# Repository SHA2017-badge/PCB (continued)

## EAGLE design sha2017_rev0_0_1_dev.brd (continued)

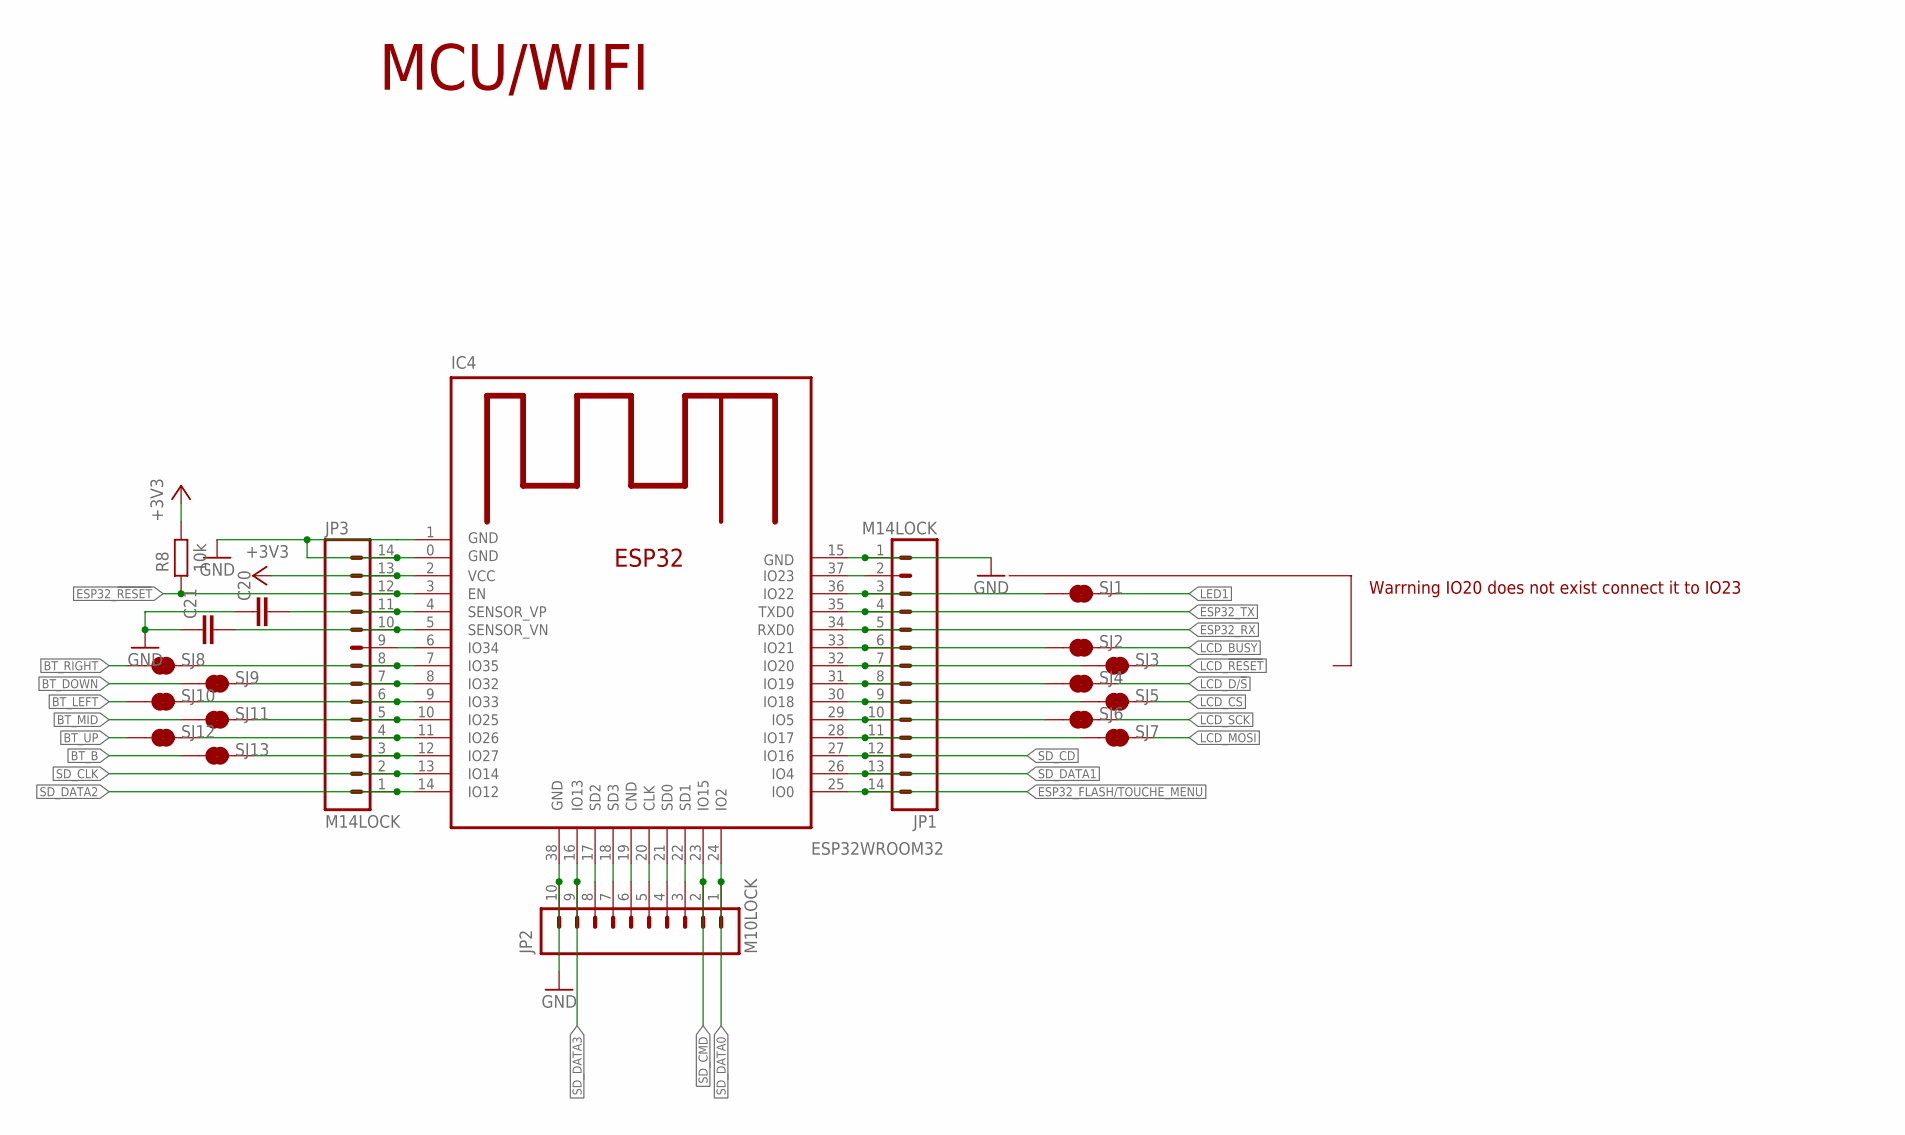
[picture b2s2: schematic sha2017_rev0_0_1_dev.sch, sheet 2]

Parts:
C20, C21: C-EUC0603; C0603
IC4: ESP32WROOM32; ESP32MOD
JP1, JP3: M14LOCK; 1X14_LOCK
JP2: M10LOCK; 1X10_LOCK
R8: 10k; R0603; PARTNO ERJ-3GEYJ103V
SJ1, SJ2, SJ3, SJ4, SJ5, SJ6, SJ7, SJ8, SJ9, SJ10, SJ11, SJ12, SJ13: JUMPER-PAD-2-NC_BY_TRACE; PAD-JUMPER-2-NC_BY_TRACE_YES_SILK

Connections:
+3V3: IC4.2 (VCC), JP3.13, R8.1; also elsewhere on the board
BT_B: SJ13.1; also elsewhere on the board
BT_DOWN: SJ9.1; also elsewhere on the board
BT_LEFT: SJ10.1; also elsewhere on the board
BT_MID: SJ11.1; also elsewhere on the board
BT_RIGHT: SJ8.1; also elsewhere on the board
BT_UP: SJ12.1; also elsewhere on the board
ESP32_!RESET: IC4.3 (EN), JP3.12, R8.2; also elsewhere on the board
ESP32_FLASH/TOUCHE_MENU: IC4.25 (IO0), JP1.14; also elsewhere on the board
ESP32_RX: IC4.34 (RXD0), JP1.5; also elsewhere on the board
ESP32_TX: IC4.35 (TXD0), JP1.4; also elsewhere on the board
GND: C20.1, C21.1, IC4.0 (GND), IC4.1 (GND), IC4.15 (GND), IC4.38 (GND), JP1.1, JP2.10, JP3.14; also elsewhere on the board
LCD_!RESET: SJ3.2; also elsewhere on the board
LCD_BUSY: SJ2.2; also elsewhere on the board
LCD_CS: SJ5.2; also elsewhere on the board
LCD_D/!S: SJ4.2; also elsewhere on the board
LCD_MOSI: SJ7.2; also elsewhere on the board
LCD_SCK: SJ6.2; also elsewhere on the board
LED1: SJ1.2; also elsewhere on the board
unnamed: IC4.6 (IO34), JP3.9
unnamed: IC4.17 (SD2), JP2.8
unnamed: IC4.18 (SD3), JP2.7
unnamed: IC4.19 (CND), JP2.6
unnamed: IC4.20 (CLK), JP2.5
unnamed: IC4.21 (SD0), JP2.4
unnamed: IC4.22 (SD1), JP2.3
unnamed: IC4.37 (IO23), JP1.2
unnamed: IC4.36 (IO22), JP1.3, SJ1.1
unnamed: IC4.33 (IO21), JP1.6, SJ2.1
unnamed: IC4.32 (IO20), JP1.7, SJ3.1
unnamed: IC4.30 (IO18), JP1.9, SJ5.1
unnamed: IC4.29 (IO5), JP1.10, SJ6.1
unnamed: IC4.28 (IO17), JP1.11, SJ7.1
unnamed: C20.2, IC4.4 (SENSOR_VP), JP3.11
unnamed: C21.2, IC4.5 (SENSOR_VN), JP3.10
unnamed: IC4.7 (IO35), JP3.8, SJ8.2
unnamed: IC4.8 (IO32), JP3.7, SJ9.2
unnamed: IC4.9 (IO33), JP3.6, SJ10.2
unnamed: IC4.10 (IO25), JP3.5, SJ11.2
unnamed: IC4.11 (IO26), JP3.4, SJ12.2
unnamed: IC4.12 (IO27), JP3.3, SJ13.2
unnamed: IC4.31 (IO19), JP1.8, SJ4.1
SD_CD: IC4.27 (IO16), JP1.12; also elsewhere on the board
SD_CLK: IC4.13 (IO14), JP3.2; also elsewhere on the board
SD_CMD: IC4.23 (IO15), JP2.2; also elsewhere on the board
SD_DATA0: IC4.24 (IO2), JP2.1; also elsewhere on the board
SD_DATA1: IC4.26 (IO4), JP1.13; also elsewhere on the board
SD_DATA2: IC4.14 (IO12), JP3.1; also elsewhere on the board
SD_DATA3: IC4.16 (IO13), JP2.9; also elsewhere on the board

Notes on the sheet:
MCU/WIFI
Warrning IO20 does not exist connect it to IO23

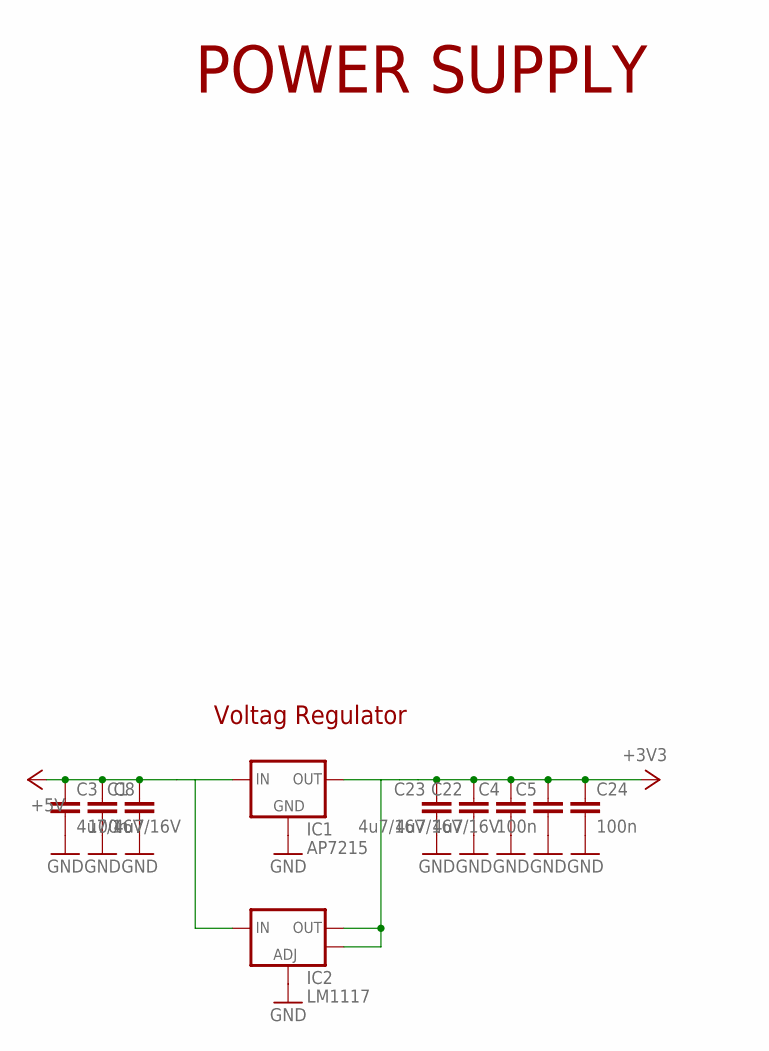
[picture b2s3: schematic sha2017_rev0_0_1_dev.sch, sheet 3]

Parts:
C1, C5, C24: 100n; C0603; PARTNO GRM188R71H104KA93D
C3, C4, C8, C22, C23: 4u7/16V; C0805; PARTNO GRM21BR61C475KA88K
IC1: AP7215; SOT89; PARTNO AP7215-33YG-13
IC2: LM1117; SOT223; PARTNO LM1117MPX-3.3/NOPB

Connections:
+3V3: C4.1, C5.1, C22.1, C23.1, C24.1, IC1.3 (OUT), IC2.2 (OUT), IC2.4 (OUT); also elsewhere on the board
+5V: C1.1, C3.1, C8.1, IC1.2 (IN), IC1.2@ (IN), IC2.3 (IN); also elsewhere on the board
GND: C1.2, C3.2, C4.2, C5.2, C8.2, C22.2, C23.2, C24.2, IC1.1 (GND), IC2.1 (ADJ); also elsewhere on the board

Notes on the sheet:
Voltag Regulator
POWER SUPPLY

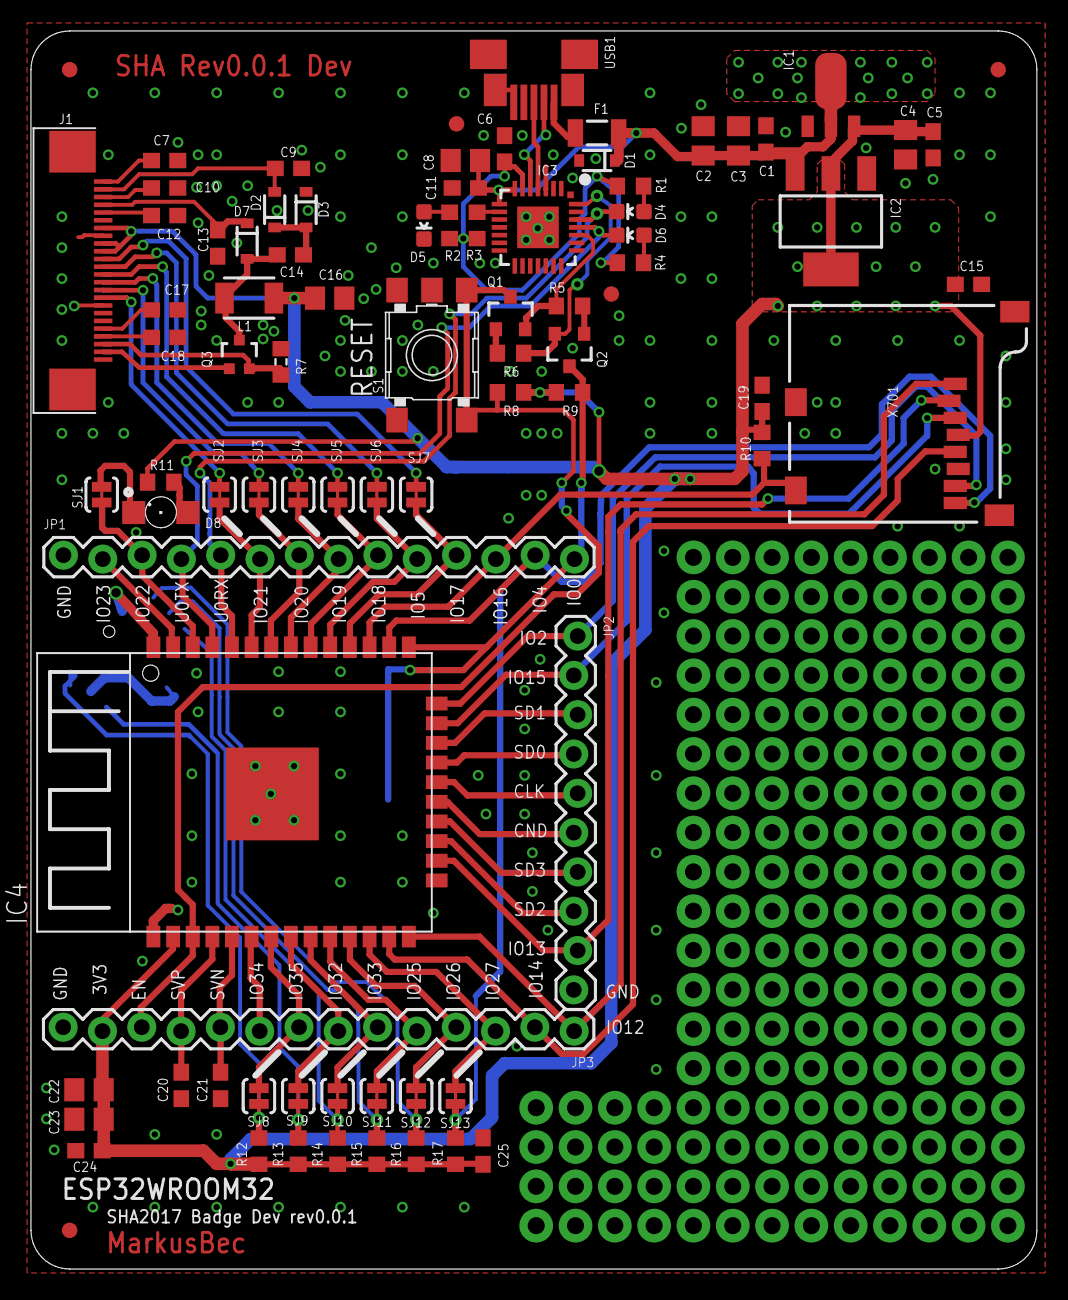
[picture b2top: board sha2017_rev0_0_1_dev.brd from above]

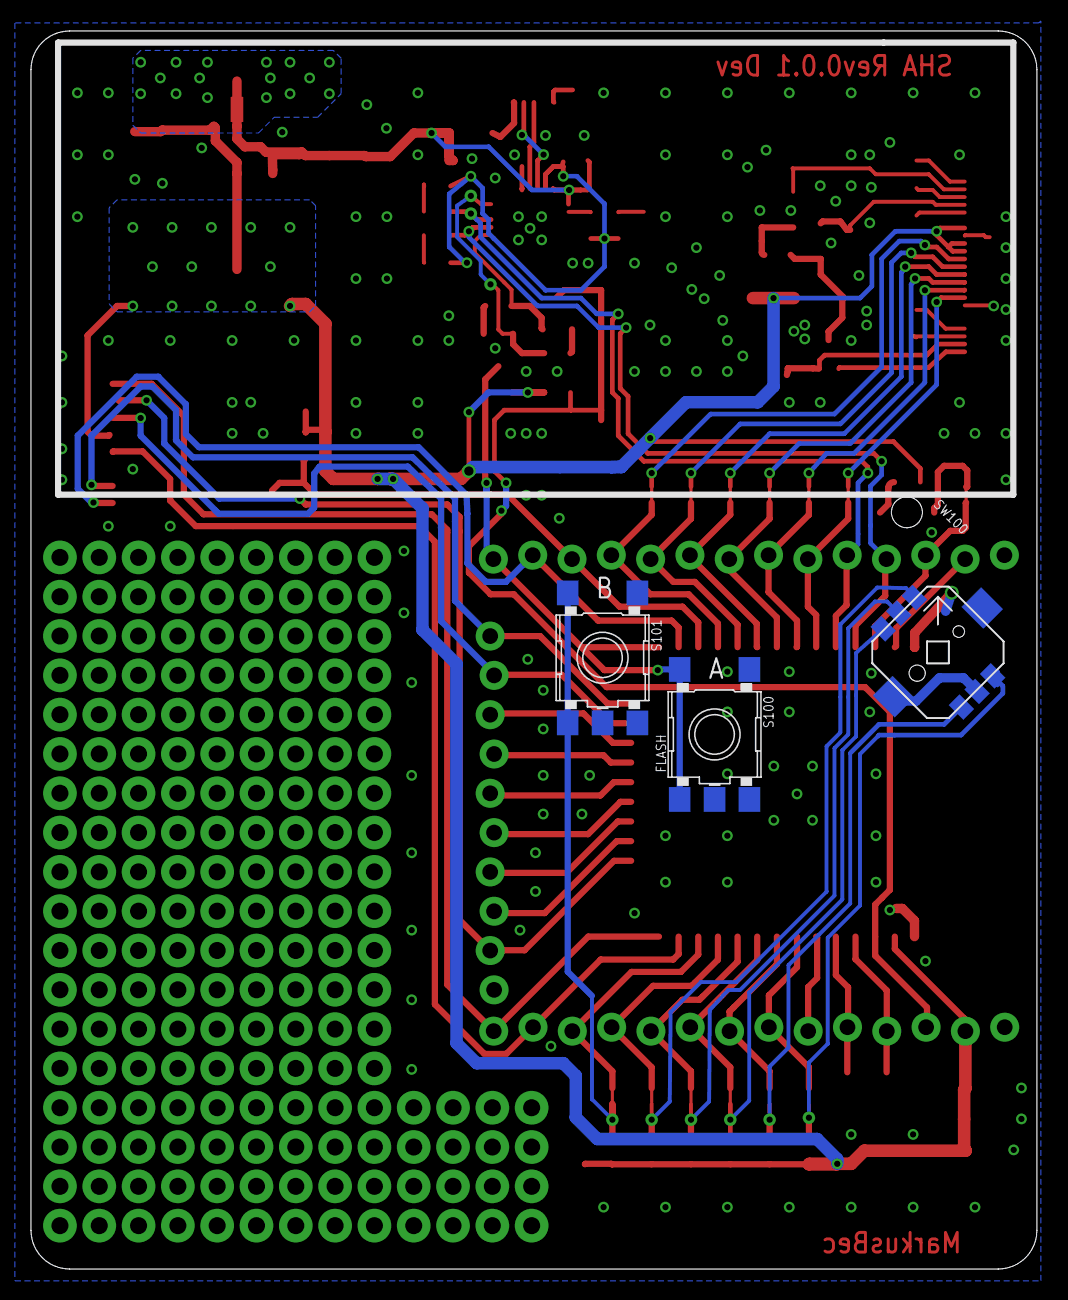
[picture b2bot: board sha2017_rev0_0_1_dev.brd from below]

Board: 2 copper layers, 65.0 x 80.0 mm, 87 parts (3 on the bottom side), 74 nets.

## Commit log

2016-09-14 initial beta Schematics
2016-09-14 add esp32 pinout
2016-09-14 schematic Cleanup adding MPU6050
2016-09-21 minimal Dev version to verify the e-paper display
2016-09-21 Moved files around
2016-09-21 add pinout for the lcd added usb status leds
2016-09-22 initial PCB design
2016-09-22 removed dedicated flash switch, switch A will be now flash and switch A.
2016-09-22 all parts places minor adjustments needed
2016-09-23 finished routing. Part designators needs to be fixed
2016-09-23 fixed all part designators
2016-09-24 some PCB tweeking
2016-10-17 changed ESP module to WROOM32
2016-10-17 fixed silkscreen
2016-10-18 Added text
2016-10-19 added markings
2016-10-25 add gerber produktion data
2016-12-01 Swapped NC and IO23
2016-12-01 Bumped version
2017-01-18 Produktion Version of the first badge prototyp
    errata
    IO20 does not exsist
    Connect it to IO23
2017-01-18 Initial Commit Of Version 0.1.0
    First full funktional Prototyp with battery and charger.
    Still some routing work to do.
2017-01-21 placed most of the parts
2017-01-25 finised routing
2017-01-25 removed some drc errors and add feducials
2017-01-25 add spezial vias to touch arrea to trick DRC
2017-01-26 added most of the test points
2017-01-26 renumbered PCB and placed designators
2017-01-26 added SDIO pullups and some bootstrap magic for it
2017-01-26 replaced transistor with a diode becaus we need it non inverting
2017-01-26 add solder briges to unused IOs at 1 Wire SDiomode (roosted: MIMIMI I WANT MORE IOS!!!!!)
2017-01-26 fixed designators
2017-01-27 some small fixes
2017-01-27 cleanup an Testpoint marking
2017-01-28 add 1 LED
2017-01-30 add initial BOM
2017-01-30 adjusted values and add moe coper to the charger region
2017-01-30 MOOOOOOOORRRRREEEEEEE VIAS for the charger
2017-01-30 fixed bug at powersupply Mosfets was N channel and need to be P channel to switch the Highside voltage
2017-01-30 fixed pinswap at sd card
2017-01-30 changes via styl for net DATA1
2017-01-30 added 4,7µF decopling capacitor to the cpt112s power rails
2017-01-30 minor adjustments
2017-01-30 SD pullups to 3V3_SWITCHED
2017-01-30 Added some artwork
2017-01-30 fixing broken ground plane
2017-01-31 Removed intermediate dimensions, added PDF
2017-01-31 add some color
2017-01-31 add missin ground via at cpt112 programming interface
2017-02-01 Design Freeze
2017-04-07 fixed some values
2017-04-07 some more changes
2017-04-23 Reorganize gerber
2017-04-23 Replace charge controller, cleaned up schematic
2017-04-24 Swap port expander and CPT112S for MPR121
2017-04-24 Replace BJTs by AO3400 nFET
2017-04-24 Fix r10
2017-04-24 Update PDF
2017-04-25 Removed unnecessary MOSFETs
2017-04-26 Finalized LED and SD card power switches, rerouted
2017-04-26 Reroute touch controller
2017-04-27 Reverted power switches, re-routed touch controller
2017-04-27 Fix schematic
2017-04-27 Fix airwire
2017-04-27 MarkusBec rerouting and fixes
2017-04-27 Board change
2017-04-27 Center trace
2017-04-27 R2 0603->1206
2017-04-27 Extra vreg (not routed\!)
2017-04-27 Replace vreg
2017-04-27 Gerbers, design freeze
2017-05-06 Update README with new board version
2017-05-07 Fix short, add silkscreen logo
2017-05-07 Fixed DRU Fixed routing adjust lables and increase size
2017-05-07 rerout extio-4 and added register holes ext socket
2017-05-07 some fixes
2017-05-08 Add option for GD/DKE displays - TODO: ROUTE
2017-05-08 routing of display option
2017-05-10 Add 1_0_1 PDFs
2017-05-18 FINAL gerbers, design freeze
2017-05-27 Panel gerbers
2017-06-09 Add assembly component drawing
2017-06-14 small proto board for the sha badge
2017-07-15 add rev0.0.2 schematic pdf
2017-08-23 Add final BOM
2017-12-08 Create license
